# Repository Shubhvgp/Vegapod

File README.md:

Hey Guys, I have created this repository to store what we have accomplished this year and what we did last year as well. 
It is a simple method to keep track of whats going on in Vegapod in each department.
There is a folder named Task Upload, where all recruits from thier respective departments will upload whatever major task they have accomplished.
I want to see this repository being updated everyday.
ALRIGHT, ENOUGH CHATTING, OFF WE GO!!! (to work ofc :] )

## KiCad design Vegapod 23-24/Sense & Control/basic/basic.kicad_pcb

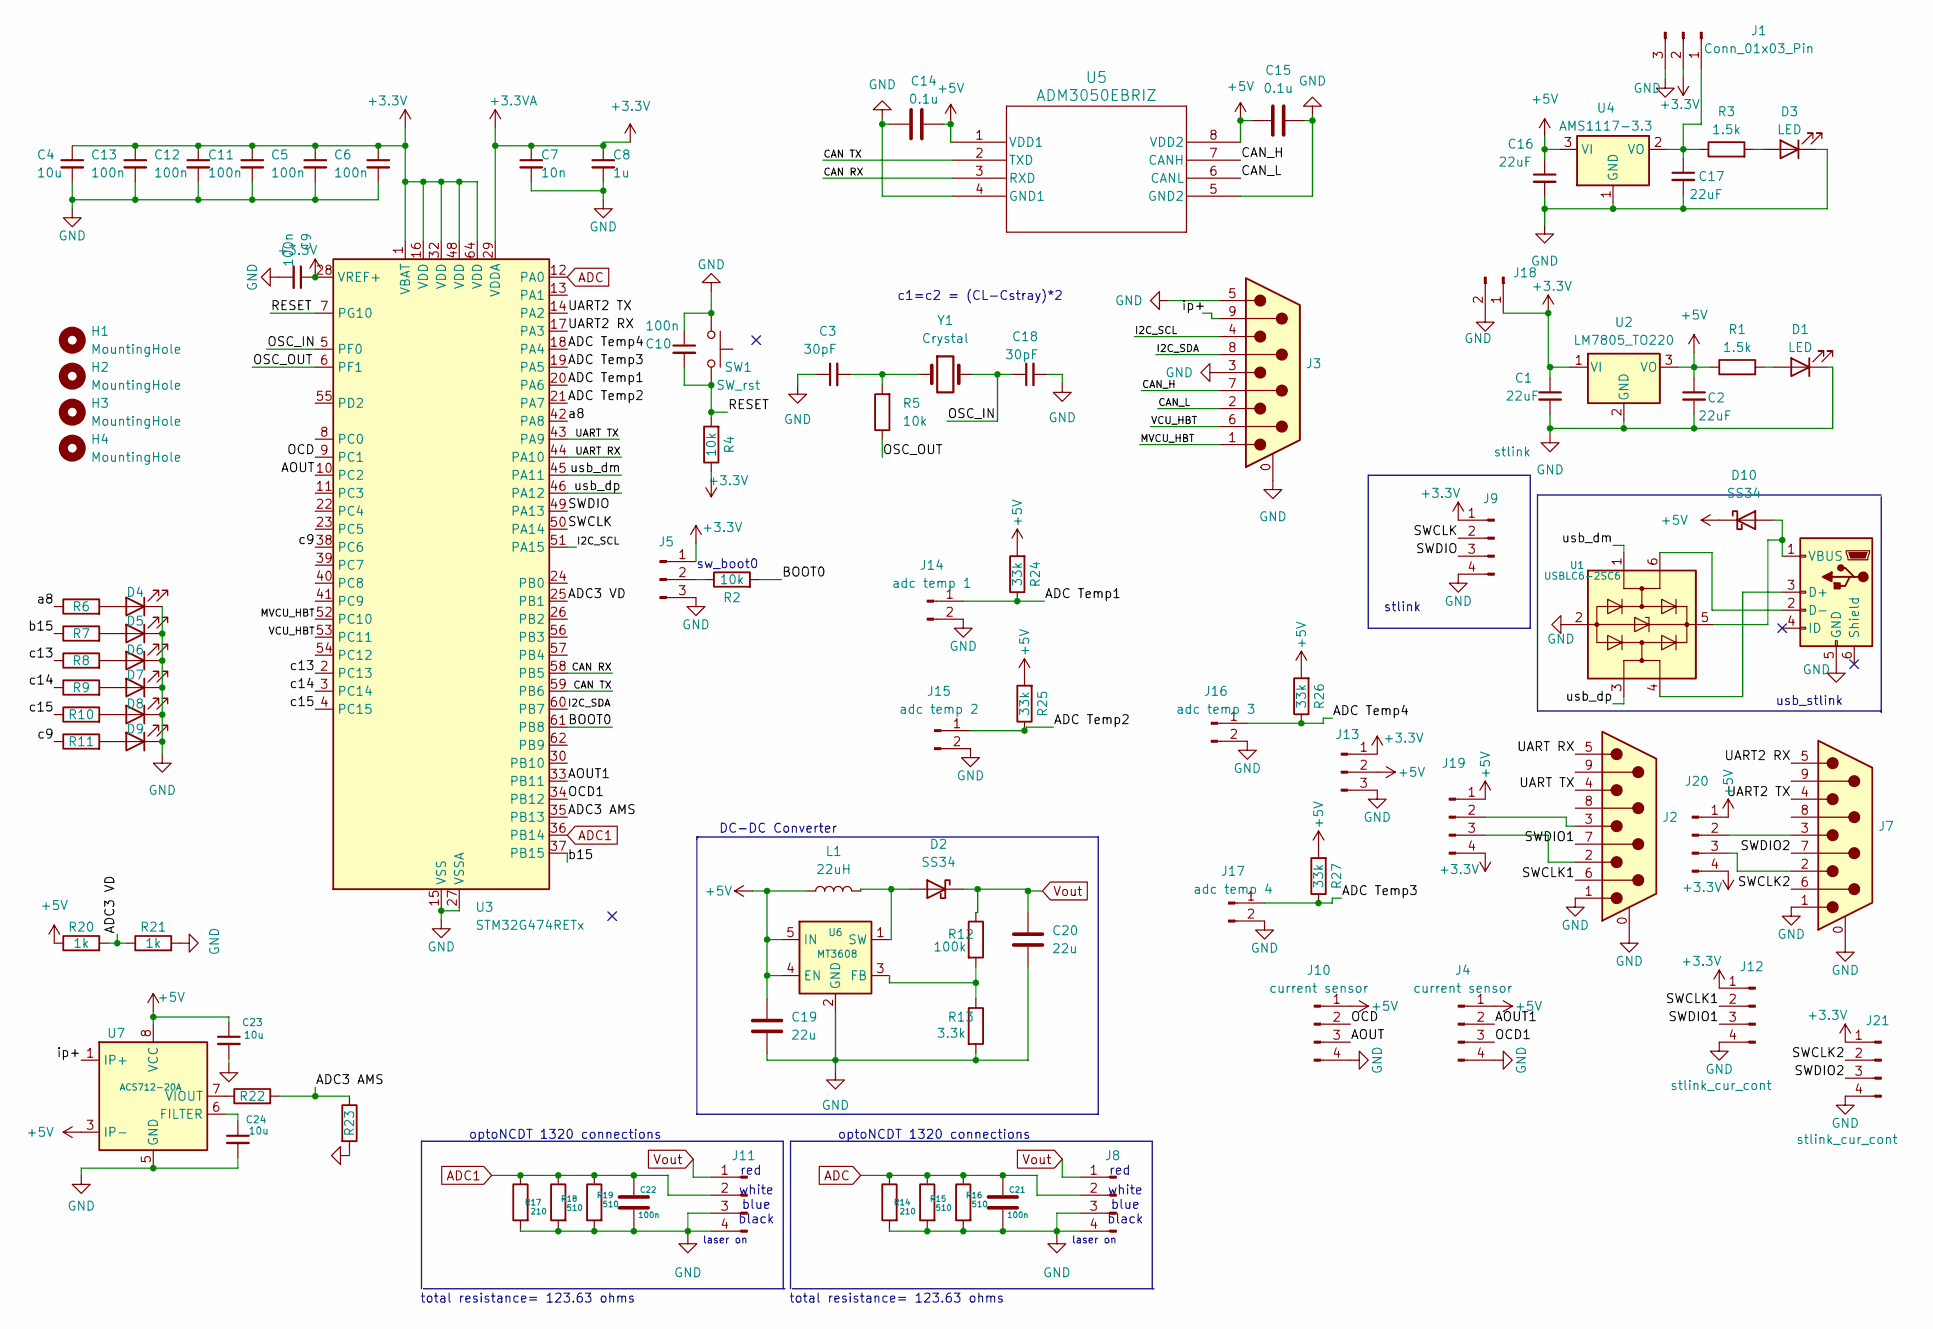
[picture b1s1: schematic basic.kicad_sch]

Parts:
C1, C2, C16, C17: 22uF; C_0805_2012Metric_Pad1.18x1.45mm_HandSolder
C3, C18: 30pF; C_0805_2012Metric_Pad1.18x1.45mm_HandSolder
C4, C23, C24: 10u; C_0805_2012Metric_Pad1.18x1.45mm_HandSolder
C5, C6, C9, C10, C11, C12, C13, C21, C22: 100n; C_0805_2012Metric_Pad1.18x1.45mm_HandSolder
C7: 10n; C_0805_2012Metric_Pad1.18x1.45mm_HandSolder
C8: 1u; C_0805_2012Metric_Pad1.18x1.45mm_HandSolder
C14, C15: 0.1u; C_0805_2012Metric_Pad1.18x1.45mm_HandSolder
C19, C20: 22u; C_1206_3216Metric_Pad1.33x1.80mm_HandSolder
D1, D3, D4, D5, D6, D7, D8, D9: LED; LED_0805_2012Metric_Pad1.15x1.40mm_HandSolder
D2: SS34; D_SMA_Handsoldering
D10: SS34; D_SMA-SMB_Universal_Handsoldering
H1, H2, H3, H4: MountingHole; MountingHole_3.2mm_M3
J1, J5, J13: Conn_01x03_Pin; PinHeader_1x03_P2.54mm_Vertical
J2, J3, J7: DE9_Plug_MountingHoles; DSUB-9_Male_Horizontal_P2.77x2.84mm_EdgePinOffset4.94mm_Hou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
J4, J10: current sensor; TerminalBlock_Phoenix_MKDS-1,5-4_1x04_P5.00mm_Horizontal
J6: USB_B_Micro; USB_Micro-B_Amphenol_10118193-0002LF_Horizontal
J8, J11: conn to air gap sensor; TerminalBlock_Phoenix_MKDS-1,5-4_1x04_P5.00mm_Horizontal
J9: stlink; PinHeader_1x04_P2.54mm_Horizontal
J12, J21: stlink_cur_cont; PinHeader_1x04_P2.54mm_Vertical
J14: adc temp 1; PinHeader_1x02_P2.54mm_Vertical
J15: adc temp 2; PinHeader_1x02_P2.54mm_Vertical
J16: adc temp 3; PinHeader_1x02_P2.54mm_Vertical
J17: adc temp 4; PinHeader_1x02_P2.54mm_Vertical
J18: Conn_01x02_Pin; TerminalBlock_Phoenix_MKDS-1,5-2-5.08_1x02_P5.08mm_Horizont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
J19, J20: current sensor; PinHeader_1x04_P2.54mm_Vertical
L1: 22uH; L_10.4x10.4_H4.8
R1, R3: 1.5k; R_0805_2012Metric_Pad1.20x1.40mm_HandSolder
R2, R4, R5: 10k; R_0805_2012Metric_Pad1.20x1.40mm_HandSolder
R6, R7, R8, R9, R10, R11, R20, R21, R22, R23: 1k; R_0805_2012Metric_Pad1.20x1.40mm_HandSolder
R12: 100k; R_0805_2012Metric_Pad1.20x1.40mm_HandSolder
R13: 3.3k; R_0805_2012Metric_Pad1.20x1.40mm_HandSolder
R14, R17: 210; R_0805_2012Metric_Pad1.20x1.40mm_HandSolder
R15, R16, R18, R19: 510; R_0805_2012Metric_Pad1.20x1.40mm_HandSolder
R24, R25, R26, R27: 33k; R_0805_2012Metric_Pad1.20x1.40mm_HandSolder
SW1: SW_rst; SW_PUSH_6mm_H5mm
U1: USBLC6-2SC6; SOT-23-6
U2: LM7805_TO220; TO-220-3_Vertical
U3: STM32G474RETx; LQFP-64_10x10mm_P0.5mm
U4: AMS1117-3.3; SOT-223-3_TabPin2
U5: ADM3050EBRIZ; RI-8-1_ADI-L
U6: MT3608; SOT-23-6
U7: ACS712-20A; SOIC-8_3.9x4.9mm_P1.27mm
Y1: Crystal; Crystal_HC49-U_Vertical

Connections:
+3.3V: C1.1, C4.1, C5.1, C6.1, C7.1, C8.1, C9.1, C11.1, C12.1, C13.1, J1.2, J5.1, J9.1, J12.1, J13.1, J18.1, J19.4, J20.4, J21.1, R4.1, U2.1 (VI), U3.1 (VBAT), U3.16 (VDD), U3.28 (VREF+), U3.29 (VDDA), U3.32 (VDD), U3.48 (VDD), U3.64 (VDD)
+5V: C2.1, C14.2, C15.2, C16.1, C19.1, C23.1, D10.1 (K), J4.1, J10.1, J13.2, J19.1, J20.1, L1.1, R1.1, R20.1, R24.2, R25.2, R26.2, R27.2, U2.3 (VO), U4.3 (VI), U5.1 (VDD1), U5.8 (VDD2), U6.4 (EN), U6.5 (IN), U7.3 (IP-), U7.4 (IP-), U7.8 (VCC)
/ADC3 AMS: R22.2, R23.1, U3.35 (PB13)
/ADC3 VD: R20.2, R21.1, U3.25 (PB1)
/ADC Temp1: J14.1, R24.1, U3.20 (PA6)
/ADC Temp2: J15.1, R25.1, U3.21 (PA7)
/ADC Temp3: J17.1, R27.1, U3.19 (PA5)
/ADC Temp4: J16.1, R26.1, U3.18 (PA4)
/AOUT: J10.3, U3.10 (PC2)
/AOUT1: J4.2, U3.33 (PB11)
/BOOT0: R2.2, U3.61 (PB8)
/CAN RX: U3.58 (PB5), U5.3 (RXD)
/CAN TX: U3.59 (PB6), U5.2 (TXD)
/CAN_H: J3.7, U5.7 (CANH)
/CAN_L: J3.2, U5.6 (CANL)
/I2C_SCL: J3.4, U3.51 (PA15)
/I2C_SDA: J3.8, U3.60 (PB7)
/MVCU_HBT: J3.1, U3.52 (PC10)
/OCD: J10.2, U3.9 (PC1)
/OCD1: J4.3, U3.34 (PB12)
/OSC_IN: C18.1, U3.5 (PF0), Y1.2
/OSC_OUT: R5.1, U3.6 (PF1)
/RESET: C10.2, R4.2, SW1.2, U3.7 (PG10)
/SWCLK: J9.2, U3.50 (PA14)
/SWCLK1: J2.6, J12.2
/SWCLK2: J7.6, J21.2
/SWDIO: J9.3, U3.49 (PA13)
/SWDIO1: J2.7, J12.3
/SWDIO2: J7.7, J21.3
/UART2 RX: J7.5, U3.17 (PA3)
/UART2 TX: J7.4, U3.14 (PA2)
/UART RX: J2.5, U3.44 (PA10)
/UART TX: J2.4, U3.43 (PA9)
/VCU_HBT: J3.6, U3.53 (PC11)
/a8: R6.1, U3.42 (PA8)
/b15: R7.1, U3.37 (PB15)
/c9: R11.1, U3.38 (PC6)
/c13: R8.1, U3.2 (PC13)
/c14: R9.1, U3.3 (PC14)
/c15: R10.1, U3.4 (PC15)
/ip+: J3.9, U7.1 (IP+), U7.2 (IP+)
/usb_dm: U1.1 (I/O1), U3.45 (PA11)
/usb_dp: U1.3 (I/O2), U3.46 (PA12)
ADC: C21.1, J8.2, R14.1, R15.1, R16.1, U3.12 (PA0)
ADC1: C22.1, J11.2, R17.1, R18.1, R19.1, U3.36 (PB14)
GND: C1.2, C2.2, C3.1, C4.2, C5.2, C6.2, C7.2, C8.2, C9.2, C10.1, C11.2, C12.2, C13.2, C14.1, C15.1, C16.2, C17.2, C18.2, C19.2, C20.2, C21.2, C22.2, C23.2, C24.2, D1.1 (K), D3.1 (K), D4.1 (K), D5.1 (K), D6.1 (K), D7.1 (K), D8.1 (K), D9.1 (K), J1.3, J2.0 (PAD), J2.1, J3.0 (PAD), J3.3, J3.5, J4.4, J5.3, J6.5 (GND), J7.0 (PAD), J7.1, J8.3, J8.4, J9.4, J10.4, J11.3, J11.4, J12.4, J13.3, J14.2, J15.2, J16.2, J17.2, J18.2, J21.4, R13.2, R14.2, R15.2, R16.2, R17.2, R18.2, R19.2, R21.2, R23.2, SW1.1, U1.2 (GND), U2.2 (GND), U3.15 (VSS), U3.27 (VSSA), U3.31 (VSS), U3.47 (VSS), U3.63 (VSS), U4.1 (GND), U5.4 (GND1), U5.5 (GND2), U6.2 (GND), U7.5 (GND)
unnamed: C3.2, R5.2, Y1.1
unnamed: D1.2 (A), R1.2
unnamed: D2.2 (A), L1.2, U6.1 (SW)
unnamed: D3.2 (A), R3.2
unnamed: D4.2 (A), R6.2
unnamed: D5.2 (A), R7.2
unnamed: D6.2 (A), R8.2
unnamed: D7.2 (A), R9.2
unnamed: D8.2 (A), R10.2
unnamed: D9.2 (A), R11.2
unnamed: D10.2 (A), J6.1 (VBUS), U1.5 (VBUS)
unnamed: C17.1, J1.1, R3.1, U4.2 (VO)
unnamed: J5.2, R2.1
unnamed: J6.3 (D+), U1.4 (I/O2)
unnamed: J6.2 (D-), U1.6 (I/O1)
unnamed: J2.3, J19.2
unnamed: J2.2, J19.3
unnamed: J7.3, J20.2
unnamed: J7.2, J20.3
unnamed: R12.2, R13.1, U6.3 (FB)
unnamed: C24.1, U7.6 (FILTER)
unnamed: R22.1, U7.7 (VIOUT)
Vout: C20.1, D2.1 (K), J8.1, J11.1, R12.1

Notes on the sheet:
optoNCDT 1320 connections
DC-DC Converter
laser on
white blue black
red
sw_boot0
total resistance= 123.63 ohms
usb_stlink
stlink
c1=c2 = (CL-Cstray)*2

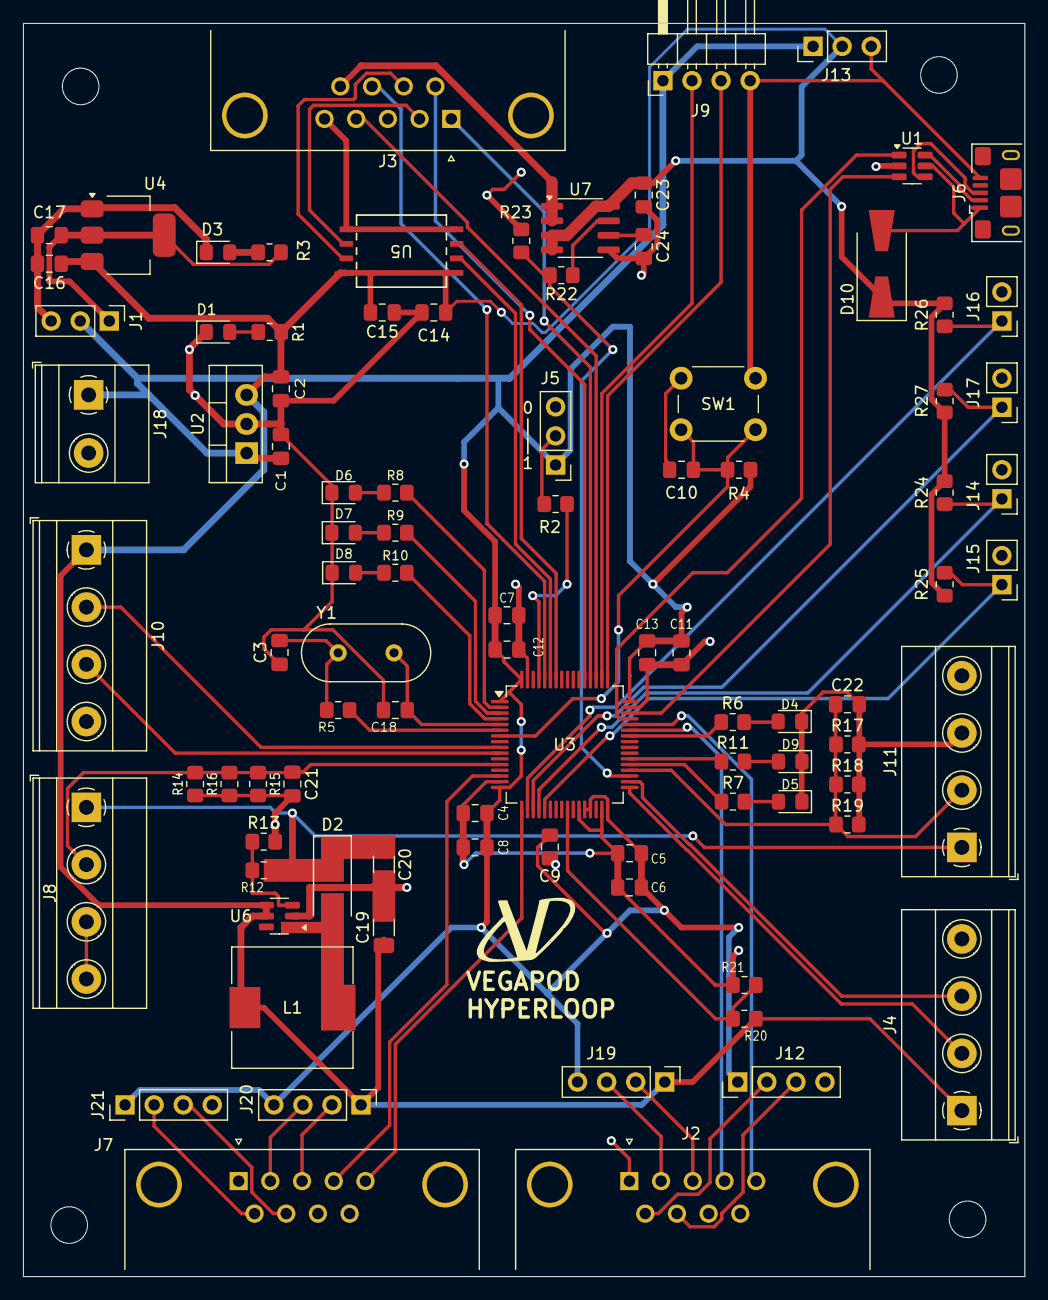
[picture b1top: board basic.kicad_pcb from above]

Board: 2 copper layers, 87.5 x 109.5 mm, 96 parts (0 on the bottom side), 69 nets.

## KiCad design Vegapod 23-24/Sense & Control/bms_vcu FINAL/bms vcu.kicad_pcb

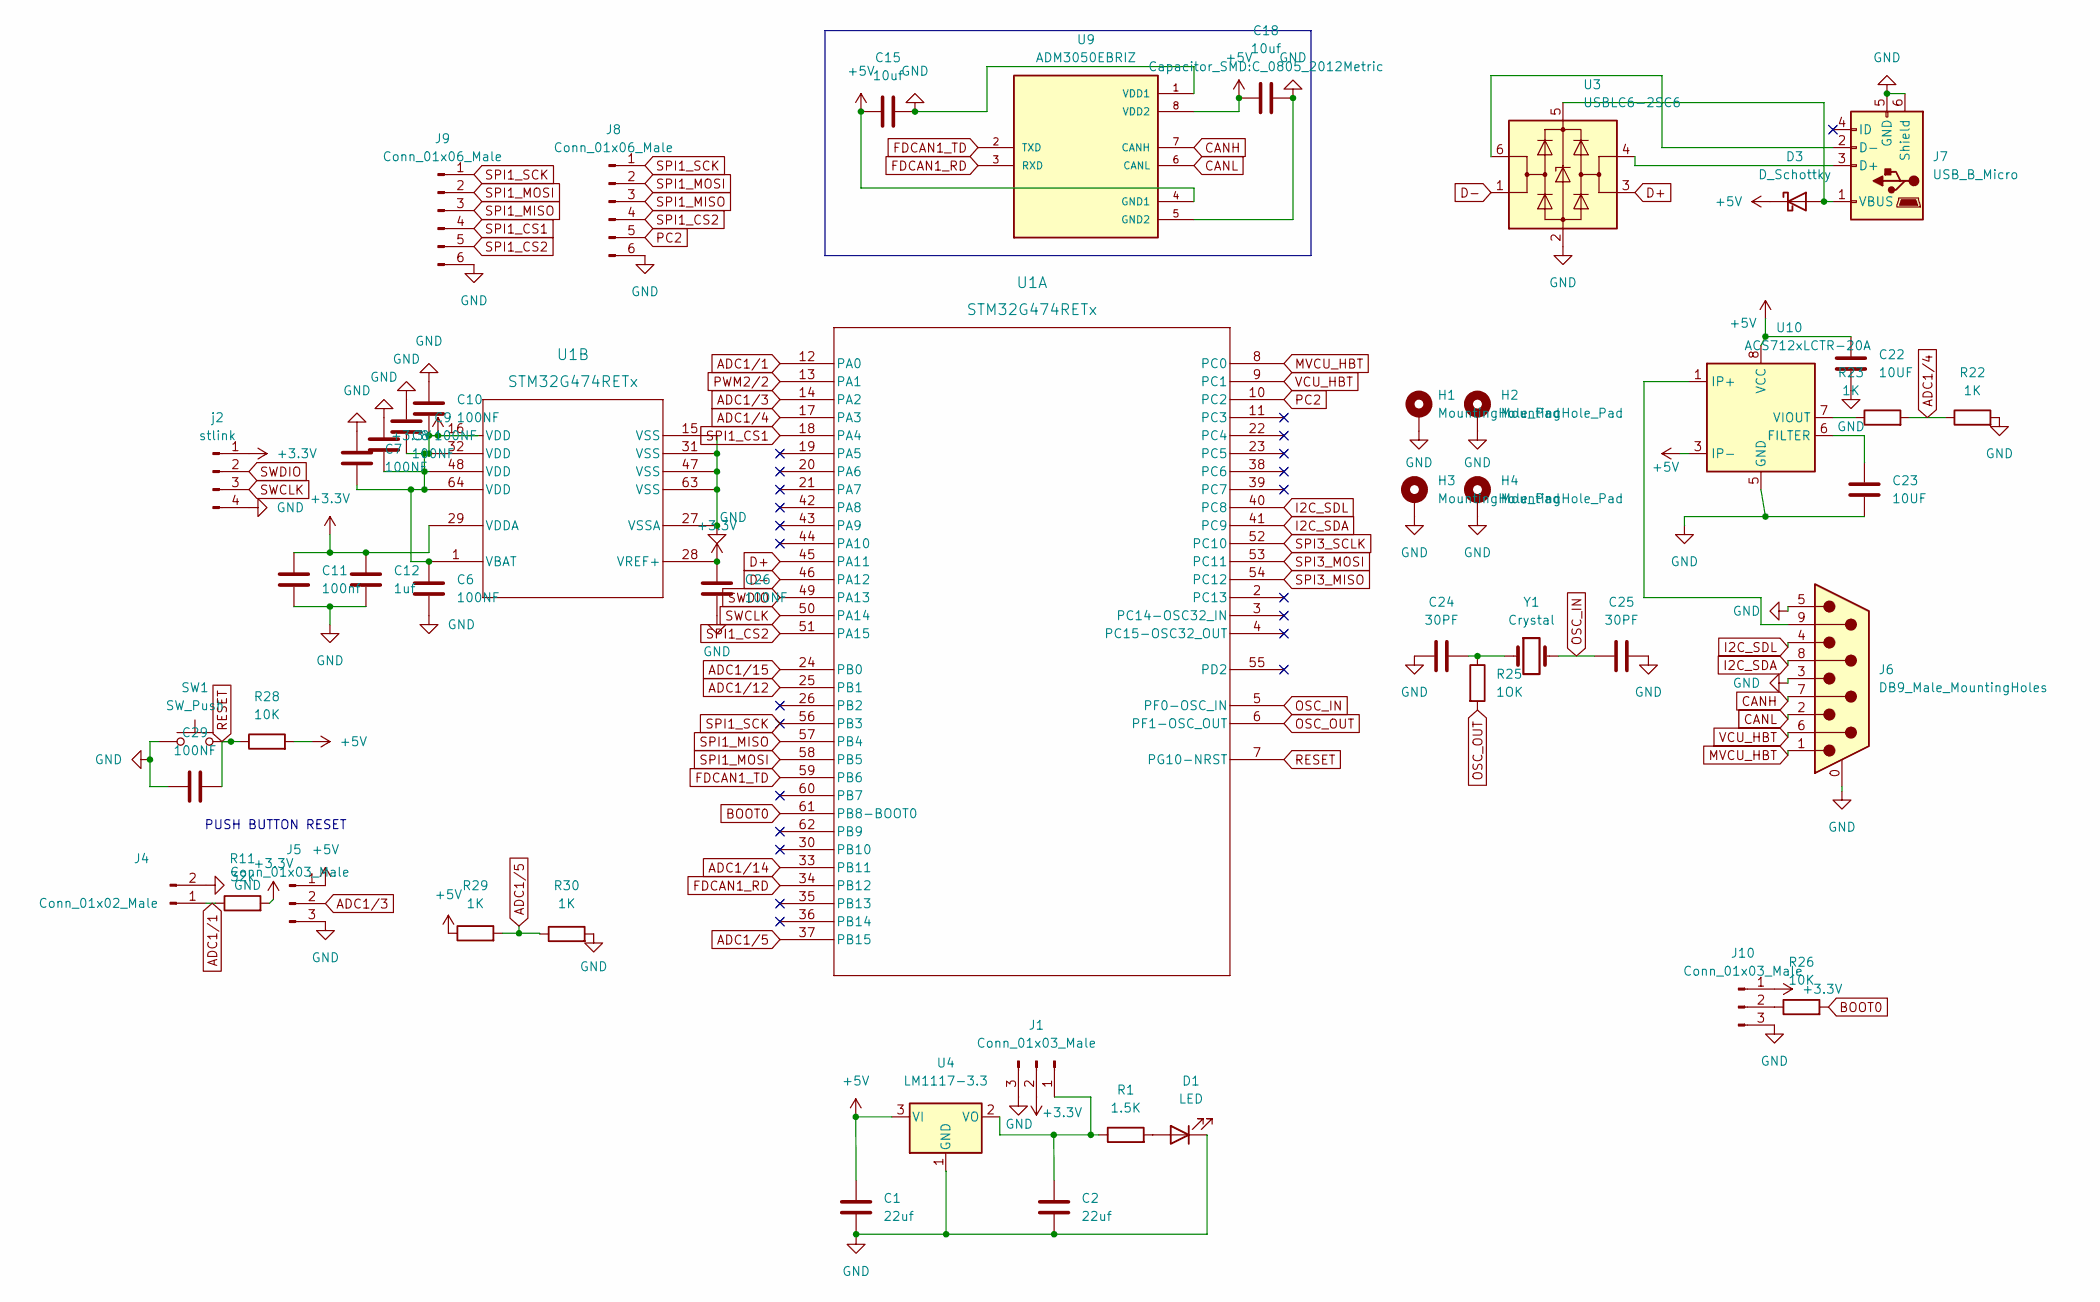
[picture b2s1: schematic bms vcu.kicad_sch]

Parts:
C1, C2: 22uf; C_0805_2012Metric
C6, C7, C8, C9, C10, C26: 100NF; C_0805_2012Metric
C11: 100nf; C_0805_2012Metric
C12: 1uf; C_0805_2012Metric
C15, C18: 10uf; C_0805_2012Metric
C22, C23: 10UF; C_1206_3216Metric
C24, C25: 30PF; C_1206_3216Metric
C29: 100NF; C_1206_3216Metric
D1: LED; LED_0603_1608Metric
D3: D_Schottky; D_2010_5025Metric
H1, H2, H3, H4: MountingHole_Pad; MountingHole_3.2mm_M3
J1, J5: Conn_01x03_Male; PinHeader_1x03_P2.54mm_Vertical
J4: Conn_01x02_Male; PinHeader_1x02_P2.54mm_Vertical
J6: DB9_Male_MountingHoles; DSUB-9_Male_Horizontal_P2.77x2.84mm_EdgePinOffset4.94mm_Hou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
J7: USB_B_Micro; USB_Micro-B_Wuerth_629105150521_CircularHoles
J8, J9: Conn_01x06_Male; JST_EH_B6B-EH-A_1x06_P2.50mm_Vertical
J10: Conn_01x03_Male; PinSocket_1x03_P2.54mm_Vertical
R1: 1.5K; R_0805_2012Metric
R11: 32k; R_0805_2012Metric
R22, R23: 1K; R_0805_2012Metric
R25: 1OK; R_1206_3216Metric
R26: 10K; R_0805_2012Metric
R28: 10K; R_1206_3216Metric
R29, R30: 1K; R_1206_3216Metric
SW1: SW_Push; SW_PUSH_6mm
U1: STM32G474RETx; LQFP64-10x10mm
U3: USBLC6-2SC6; SOT-23-6
U4: LM1117-3.3; SOT-223-3_TabPin2
U9: ADM3050EBRIZ; SOIC127P1031X265-8N; PARTREV B
U10: ACS712xLCTR-20A; SOIC-8_3.9x4.9mm_P1.27mm
Y1: Crystal; Crystal_HC18-U_Vertical
j2: stlink; PinHeader_1x04_P2.54mm_Vertical

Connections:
+3.3V: C6.1, C7.2, C8.2, C9.2, C10.2, C11.1, C12.1, C26.1, J1.2, J10.1, R11.2, U1.1 (VBAT), U1.16 (VDD), U1.28 (VREF+), U1.29 (VDDA), U1.32 (VDD), U1.48 (VDD), U1.64 (VDD), j2.1
+5V: C1.1, C15.1, C18.1, C22.1, D3.1 (K), J5.1, R28.2, R29.1, U4.3 (VI), U9.4 (GND1), U9.8 (VDD2), U10.3 (IP-), U10.4 (IP-), U10.8 (VCC)
ADC1/1: J4.1, R11.1, U1.12 (PA0)
ADC1/3: J5.2, U1.14 (PA2)
ADC1/4: R22.1, R23.2, U1.17 (PA3)
ADC1/5: R29.2, R30.1, U1.37 (PB15)
ADC1/12: U1.25 (PB1)
ADC1/14: U1.33 (PB11)
ADC1/15: U1.24 (PB0)
BOOT0: R26.2, U1.61 (PB8-BOOT0)
CANH: J6.7, U9.7 (CANH)
CANL: J6.2, U9.6 (CANL)
D+: U1.45 (PA11), U3.3 (I/O2)
D-: U1.46 (PA12), U3.1 (I/O1)
FDCAN1_RD: U1.34 (PB12), U9.3 (RXD)
FDCAN1_TD: U1.59 (PB6), U9.2 (TXD)
GND: C1.2, C2.2, C6.2, C7.1, C8.1, C9.1, C10.1, C11.2, C12.2, C15.2, C18.2, C22.2, C23.2, C24.1, C25.2, C26.2, C29.1, D1.1 (K), H1.1, H2.1, H3.1, H4.1, J1.3, J4.2, J5.3, J6.0 (PAD), J6.3, J6.5, J7.5 (GND), J7.6 (Shield), J8.6, J9.6, J10.3, R22.2, R30.2, SW1.1, U1.15 (VSS), U1.27 (VSSA), U1.31 (VSS), U1.47 (VSS), U1.63 (VSS), U3.2 (GND), U4.1 (GND), U9.1 (VDD1), U9.5 (GND2), U10.5 (GND), j2.4
I2C_SDA: J6.8, U1.41 (PC9)
I2C_SDL: J6.4, U1.40 (PC8)
MVCU_HBT: J6.1, U1.8 (PC0)
unnamed: C2.1, J1.1, R1.1, U4.2 (VO)
unnamed: C23.1, U10.6 (FILTER)
unnamed: C24.2, R25.1, Y1.1
unnamed: D1.2 (A), R1.2
unnamed: D3.2 (A), J7.1 (VBUS), U3.5 (VBUS)
unnamed: J6.9, U10.1 (IP+), U10.2 (IP+)
unnamed: J7.2 (D-), U3.6 (I/O1)
unnamed: J7.3 (D+), U3.4 (I/O2)
unnamed: J10.2, R26.1
unnamed: R23.1, U10.7 (VIOUT)
OSC_IN: C25.1, U1.5 (PF0-OSC_IN), Y1.2
OSC_OUT: R25.2, U1.6 (PF1-OSC_OUT)
PC2: J8.5, U1.10 (PC2)
PWM2/2: U1.13 (PA1)
RESET: C29.2, R28.1, SW1.2, U1.7 (PG10-NRST)
SPI1_CS1: J9.4, U1.18 (PA4)
SPI1_CS2: J8.4, J9.5, U1.51 (PA15)
SPI1_MISO: J8.3, J9.3, U1.57 (PB4)
SPI1_MOSI: J8.2, J9.2, U1.58 (PB5)
SPI1_SCK: J8.1, J9.1, U1.56 (PB3)
SPI3_MISO: U1.54 (PC12)
SPI3_MOSI: U1.53 (PC11)
SPI3_SCLK: U1.52 (PC10)
SWCLK: U1.50 (PA14), j2.3
SWDIO: U1.49 (PA13), j2.2
VCU_HBT: J6.6, U1.9 (PC1)

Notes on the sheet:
PUSH BUTTON RESET

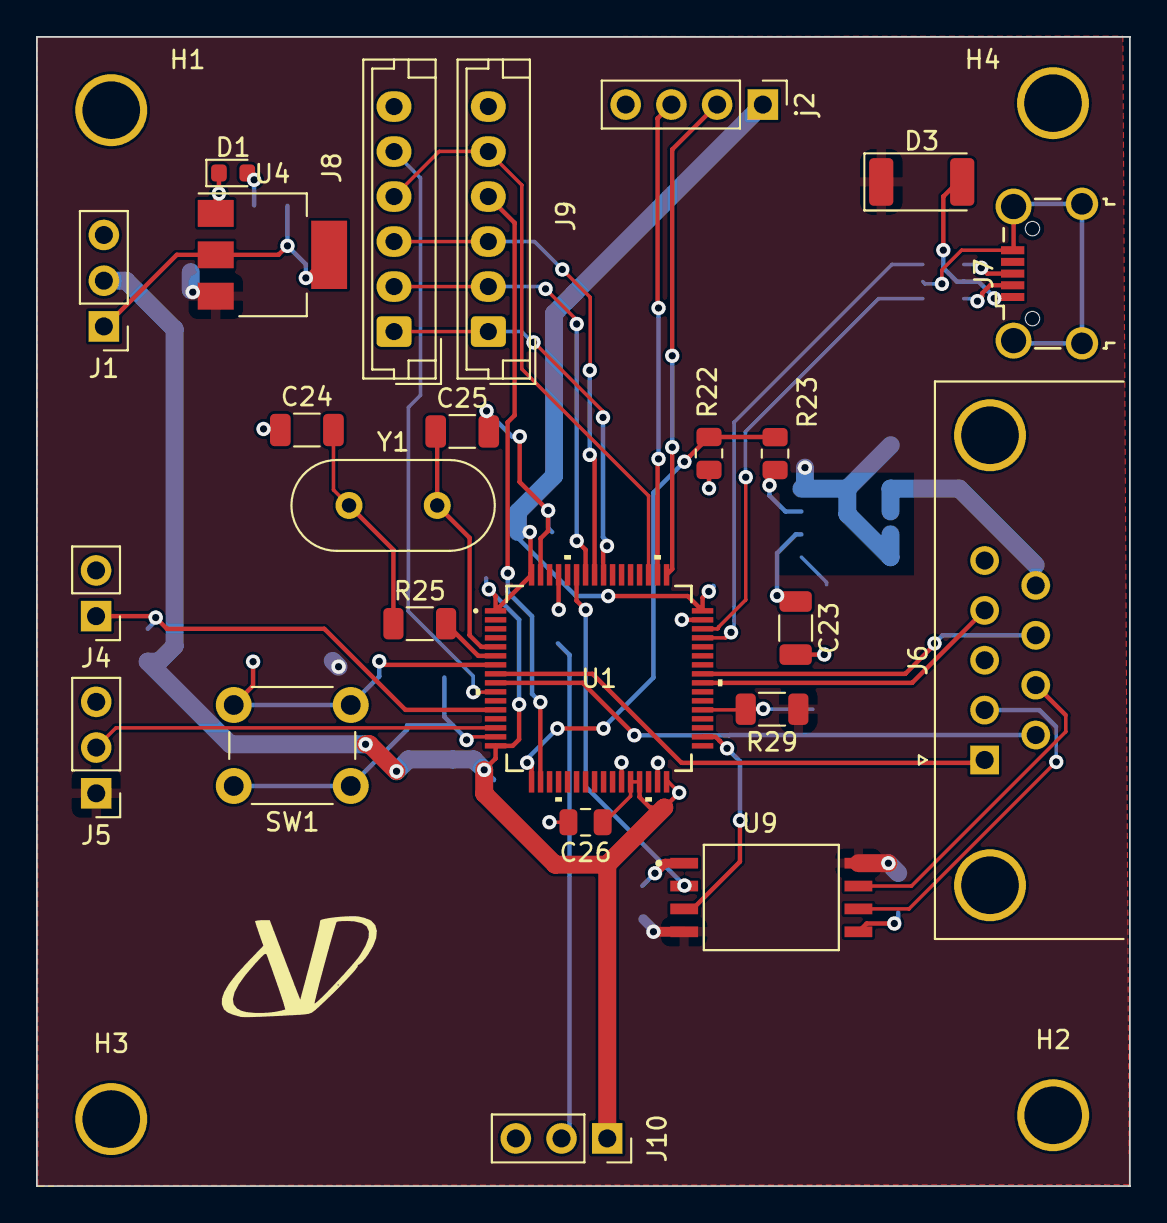
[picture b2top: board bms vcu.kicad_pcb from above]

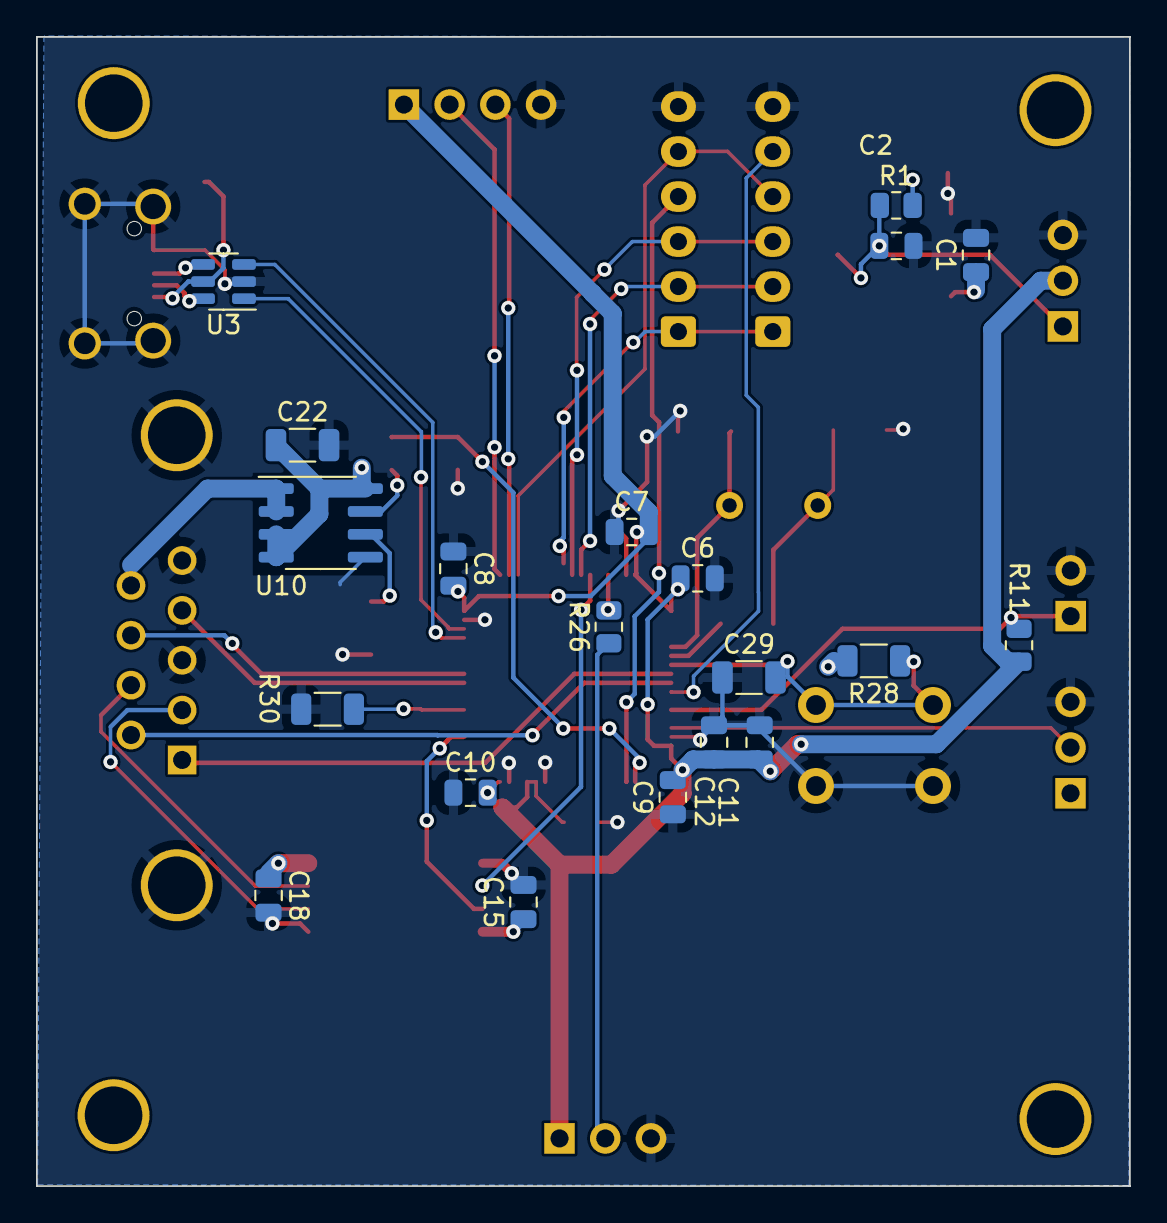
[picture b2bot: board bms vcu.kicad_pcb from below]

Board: 2 copper layers, 60.7 x 63.8 mm, 48 parts (20 on the bottom side), 39 nets.

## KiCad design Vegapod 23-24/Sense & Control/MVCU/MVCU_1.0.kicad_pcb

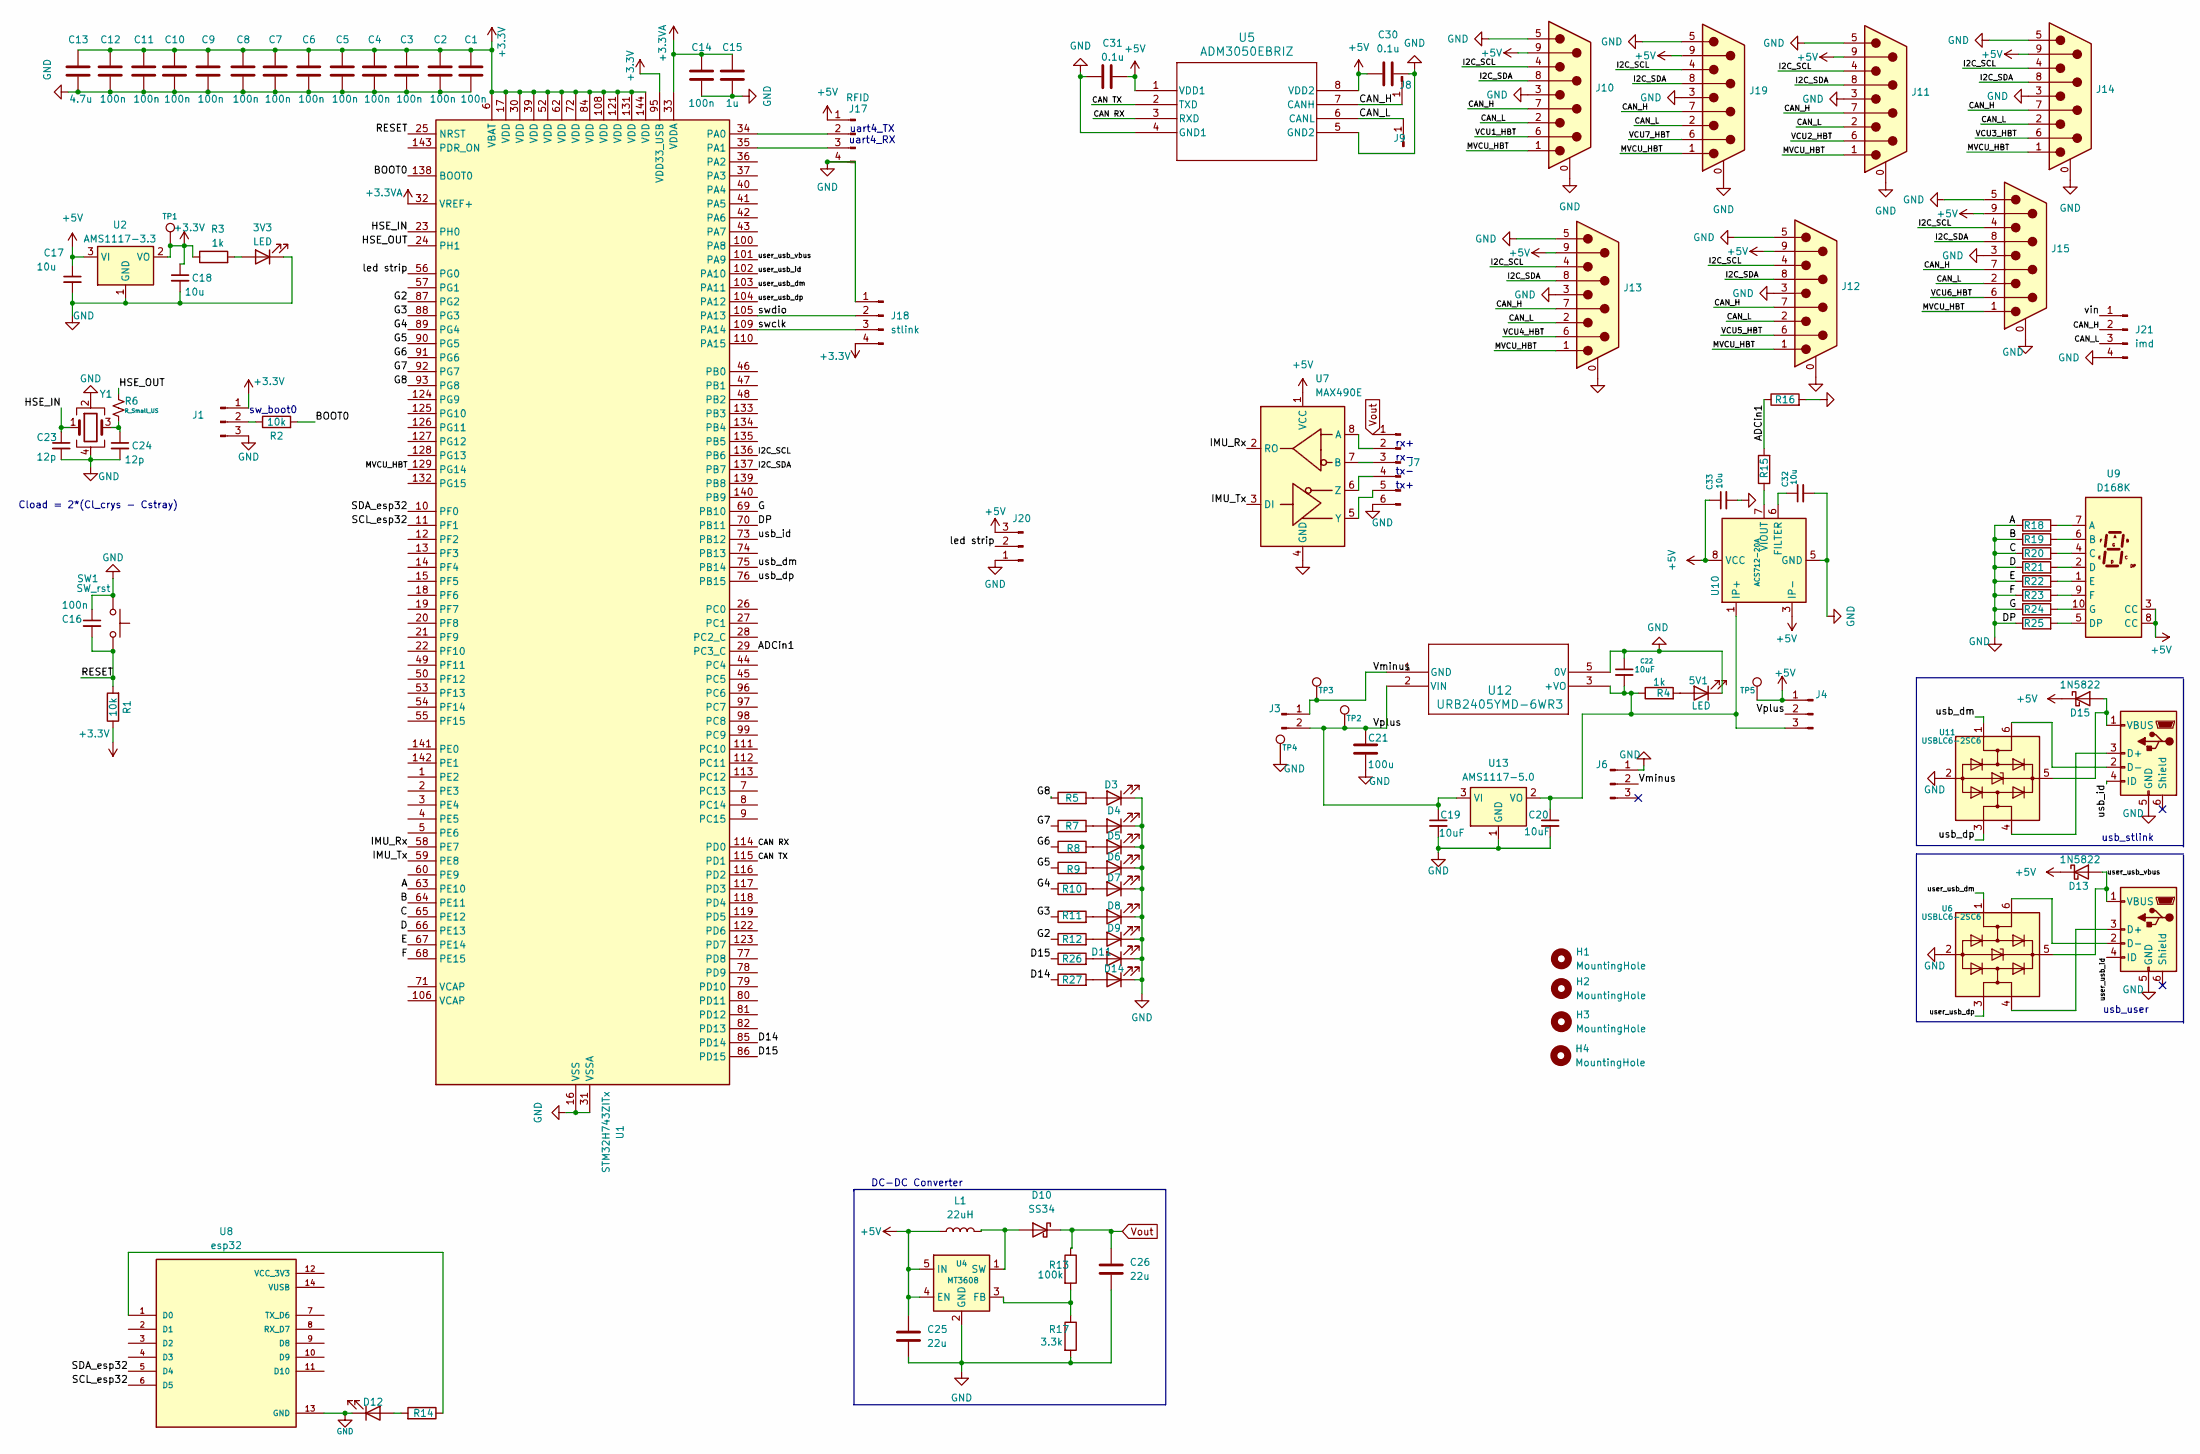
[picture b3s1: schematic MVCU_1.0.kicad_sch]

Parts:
3V3, 5V1: LED; LED_0805_2012Metric_Pad1.15x1.40mm_HandSolder
C1, C2, C3, C4, C5, C6, C7, C8, C9, C10, C11, C12, C14, C16: 100n; C_0805_2012Metric_Pad1.18x1.45mm_HandSolder
C13: 4.7u; C_0805_2012Metric_Pad1.18x1.45mm_HandSolder
C15: 1u; C_0805_2012Metric_Pad1.18x1.45mm_HandSolder
C17, C18, C32, C33: 10u; C_0805_2012Metric_Pad1.18x1.45mm_HandSolder
C19, C20: 10uF; C_0805_2012Metric_Pad1.18x1.45mm_HandSolder
C21: 100u; CP_Radial_D8.0mm_P2.50mm
C22: 10uF; CP_Radial_D8.0mm_P2.50mm
C23, C24: 12p; C_0805_2012Metric_Pad1.18x1.45mm_HandSolder
C25, C26: 22u; C_1206_3216Metric_Pad1.33x1.80mm_HandSolder
C30, C31: 0.1u; C_0805_2012Metric_Pad1.18x1.45mm_HandSolder
D3, D4, D5, D6, D7, D8, D9, D11, D12, D14: LED; LED_0805_2012Metric_Pad1.15x1.40mm_HandSolder
D10: SS34; D_SMA_Handsoldering
D13, D15: 1N5822; D_DO-201AD_P15.24mm_Horizontal
H1, H2, H3, H4: MountingHole; MountingHole_3.2mm_M3
J1: Conn_01x03_Pin; PinHeader_1x03_P2.54mm_Vertical
J3: Conn_01x02_Pin; TerminalBlock_Phoenix_MKDS-1,5-2-5.08_1x02_P5.08mm_Horizont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
J4, J6: Conn_01x03_Pin; PinSocket_1x03_P2.54mm_Vertical
J7: Conn_01x06_Pin; TerminalBlock_Phoenix_MKDS-1,5-6-5.08_1x06_P5.08mm_Horizont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
J8, J9: Conn_01x01_Pin; PinHeader_1x01_P2.54mm_Vertical
J10, J11, J12, J13, J14, J15, J19: DE9_Plug_MountingHoles; DSUB-9_Male_Horizontal_P2.77x2.84mm_EdgePinOffset4.94mm_Hou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
J16, J22: USB_B_Micro; USB_Micro-B_Amphenol_10103594-0001LF_Horizontal
J17: RFID; PinHeader_1x04_P2.54mm_Vertical
J18: stlink; PinHeader_1x04_P2.54mm_Vertical
J20: Conn_01x03_Pin; TerminalBlock_Phoenix_MKDS-1,5-3-5.08_1x03_P5.08mm_Horizont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
J21: imd; PinHeader_1x04_P2.54mm_Vertical
L1: 22uH; L_10.4x10.4_H4.8
R1, R2: 10k; R_0805_2012Metric_Pad1.20x1.40mm_HandSolder
R3, R4, R5, R7, R8, R9, R10, R11, R12, R14, R15, R16, R26, R27: 1k; R_0805_2012Metric_Pad1.20x1.40mm_HandSolder
R6: R_Small_US; R_0805_2012Metric_Pad1.20x1.40mm_HandSolder
R13: 100k; R_0805_2012Metric_Pad1.20x1.40mm_HandSolder
R17: 3.3k; R_0805_2012Metric_Pad1.20x1.40mm_HandSolder
R18, R19, R20, R21, R22, R23, R24, R25: 220; R_0805_2012Metric_Pad1.20x1.40mm_HandSolder
SW1: SW_rst; SW_PUSH_6mm_H5mm
TP1, TP2, TP3, TP4, TP5: TestPoint; TestPoint_Keystone_5010-5014_Multipurpose
U1: STM32H743ZITx; LQFP-144_20x20mm_P0.5mm
U2: AMS1117-3.3; SOT-223-3_TabPin2
U4: MT3608; SOT-23-6
U5: ADM3050EBRIZ; RI-8-1_ADI-M
U6, U11: USBLC6-2SC6; SOT-23-6
U7: MAX490E; SOIC-8_3.9x4.9mm_P1.27mm
U8: esp32; MODULE_113991054; PARTREV 23/05/2022
U9: D168K; D1X8K
U10: ACS712-20A; SOIC-8_3.9x4.9mm_P1.27mm
U12: URB2405YMD-6WR3; URB_YMD-6WR3_MNS
U13: AMS1117-5.0; SOT-223-3_TabPin2
Y1: Crystal_GND24; Crystal_SMD_3225-4Pin_3.2x2.5mm_HandSoldering

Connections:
+3.3V: C1.1, C2.1, C3.1, C4.1, C5.1, C6.1, C7.1, C8.1, C9.1, C10.1, C11.1, C12.1, C13.1, C18.1, J1.1, J18.4, R1.1, R3.1, TP1.1, U1.6 (VBAT), U1.17 (VDD), U1.30 (VDD), U1.39 (VDD), U1.52 (VDD), U1.62 (VDD), U1.72 (VDD), U1.84 (VDD), U1.95 (VDD33_USB), U1.108 (VDD), U1.121 (VDD), U1.131 (VDD), U1.144 (VDD), U2.2 (VO)
+3.3VA: C14.1, C15.1, U1.32 (VREF+), U1.33 (VDDA)
+5V: C17.1, C25.1, C30.2, C31.2, C33.1, D13.1 (K), D15.1 (K), J4.1, J10.9, J11.9, J12.9, J13.9, J14.9, J15.9, J17.1, J19.9, J20.3, L1.1, TP5.1, U2.3 (VI), U4.4 (EN), U4.5 (IN), U5.1 (VDD1), U5.8 (VDD2), U7.1 (VCC), U9.3 (CC), U9.8 (CC), U10.3 (IP-), U10.4 (IP-), U10.8 (VCC)
/ADCin1: R15.2, R16.1, U1.29 (PC3_C)
/BOOT0: R2.2, U1.138 (BOOT0)
/CAN RX: U1.114 (PD0), U5.3 (RXD)
/CAN TX: U1.115 (PD1), U5.2 (TXD)
/CAN_H: J8.1, J10.7, J11.7, J12.7, J13.7, J14.7, J15.7, J19.7, J21.2, U5.7 (CANH)
/CAN_L: J9.1, J10.2, J11.2, J12.2, J13.2, J14.2, J15.2, J19.2, J21.3, U5.6 (CANL)
/D14: R27.1, U1.85 (PD14)
/D15: R26.1, U1.86 (PD15)
/G2: R12.1, U1.87 (PG2)
/G3: R11.1, U1.88 (PG3)
/G4: R10.1, U1.89 (PG4)
/G5: R9.1, U1.90 (PG5)
/G6: R8.1, U1.91 (PG6)
/G7: R7.1, U1.92 (PG7)
/G8: R5.1, U1.93 (PG8)
/HSE_IN: C23.1, U1.23 (PH0), Y1.1
/HSE_OUT: R6.1, U1.24 (PH1)
/I2C_SCL: J10.4, J11.4, J12.4, J13.4, J14.4, J15.4, J19.4, U1.136 (PB6)
/I2C_SDA: J10.8, J11.8, J12.8, J13.8, J14.8, J15.8, J19.8, U1.137 (PB7)
/IMU_Rx: U1.58 (PE7), U7.2 (RO)
/IMU_Tx: U1.59 (PE8), U7.3 (DI)
/MVCU_HBT: J10.1, J11.1, J12.1, J13.1, J14.1, J15.1, J19.1, U1.129 (PG14)
/RESET: C16.2, R1.2, SW1.2, U1.25 (NRST)
/SCL_esp32: U1.11 (PF1), U8.6 (D5)
/SDA_esp32: U1.10 (PF0), U8.5 (D4)
/VCU1_HBT: J10.6
/VCU2_HBT: J11.6
/VCU3_HBT: J14.6
/VCU4_HBT: J13.6
/VCU5_HBT: J12.6
/VCU6_HBT: J15.6
/VCU7_HBT: J19.6
/Vminus: J3.1, J6.2, TP3.1, U12.1 (GND)
/Vplus: C19.1, C21.1, J3.2, J4.2, TP2.1, U12.2 (VIN), U13.3 (VI)
/led strip: J20.2, U1.56 (PG0)
/swclk: J18.3, U1.109 (PA14)
/swdio: J18.2, U1.105 (PA13)
/usb_dm: U1.75 (PB14), U11.1 (I/O1)
/usb_dp: U1.76 (PB15), U11.3 (I/O2)
/usb_id: J22.4 (ID), U1.73 (PB12)
/user_usb_dm: U1.103 (PA11), U6.1 (I/O1)
/user_usb_dp: U1.104 (PA12), U6.3 (I/O2)
/user_usb_id: J16.4 (ID), U1.102 (PA10)
/user_usb_vbus: D13.2 (A), J16.1 (VBUS), U1.101 (PA9), U6.5 (VBUS)
/vin: J21.1
GND: 3V3.1 (K), 5V1.1 (K), C1.2, C2.2, C3.2, C4.2, C5.2, C6.2, C7.2, C8.2, C9.2, C10.2, C11.2, C12.2, C13.2, C14.2, C15.2, C16.1, C17.2, C18.2, C19.2, C20.2, C21.2, C22.1, C23.2, C24.2, C25.2, C26.2, C30.1, C31.1, C32.2, C33.2, D3.1 (K), D4.1 (K), D5.1 (K), D6.1 (K), D7.1 (K), D8.1 (K), D9.1 (K), D11.1 (K), D12.1 (K), D14.1 (K), J1.3, J6.1, J7.6, J10.0 (PAD), J10.3, J10.5, J11.0 (PAD), J11.3, J11.5, J12.0 (PAD), J12.3, J12.5, J13.0 (PAD), J13.3, J13.5, J14.0 (PAD), J14.3, J14.5, J15.0 (PAD), J15.3, J15.5, J16.5 (GND), J17.4, J18.1, J19.0 (PAD), J19.3, J19.5, J20.1, J21.4, J22.5 (GND), R16.2, R17.2, R18.1, R19.1, R20.1, R21.1, R22.1, R23.1, R24.1, R25.1, SW1.1, TP4.1, U1.16 (VSS), U1.31 (VSSA), U1.38 (VSS), U1.51 (VSS), U1.61 (VSS), U1.63 (PE10), U1.64 (PE11), U1.65 (PE12), U1.66 (PE13), U1.67 (PE14), U1.68 (PE15), U1.69 (PB10), U1.70 (PB11), U1.83 (VSS), U1.94 (VSS), U1.107 (VSS), U1.120 (VSS), U1.130 (VSS), U2.1 (GND), U4.2 (GND), U5.4 (GND1), U5.5 (GND2), U6.2 (GND), U7.4 (GND), U8.13 (GND), U10.5 (GND), U11.2 (GND), U12.5 (0V), U13.1 (GND), Y1.2, Y1.4
unnamed: 3V3.2 (A), R3.2
unnamed: 5V1.2 (A), R4.2
unnamed: C24.1, R6.2, Y1.3
unnamed: D3.2 (A), R5.2
unnamed: D4.2 (A), R7.2
unnamed: D5.2 (A), R8.2
unnamed: D6.2 (A), R9.2
unnamed: D7.2 (A), R10.2
unnamed: D8.2 (A), R11.2
unnamed: D9.2 (A), R12.2
unnamed: D10.2 (A), L1.2, U4.1 (SW)
unnamed: D11.2 (A), R26.2
unnamed: D12.2 (A), R14.2
unnamed: D14.2 (A), R27.2
unnamed: D15.2 (A), J22.1 (VBUS), U11.5 (VBUS)
unnamed: J1.2, R2.1
unnamed: C20.1, C22.2, J4.3, R4.1, U10.1 (IP+), U10.2 (IP+), U12.3 (+VO), U13.2 (VO)
unnamed: J7.2, U7.8 (A)
unnamed: J7.3, U7.7 (B)
unnamed: J7.4, U7.6 (Z)
unnamed: J7.5, U7.5 (Y)
unnamed: J16.3 (D+), U6.4 (I/O2)
unnamed: J16.2 (D-), U6.6 (I/O1)
unnamed: J17.2, U1.34 (PA0)
unnamed: J17.3, U1.35 (PA1)
unnamed: J22.3 (D+), U11.4 (I/O2)
unnamed: J22.2 (D-), U11.6 (I/O1)
unnamed: R13.2, R17.1, U4.3 (FB)
unnamed: R14.1, U8.1 (D0)
unnamed: R18.2, U9.7 (A)
unnamed: R19.2, U9.6 (B)
unnamed: R20.2, U9.4 (C)
unnamed: R21.2, U9.2 (D)
unnamed: R25.2, U9.5 (DP)
unnamed: R22.2, U9.1 (E)
unnamed: R23.2, U9.9 (F)
unnamed: R24.2, U9.10 (G)
unnamed: C32.1, U10.6 (FILTER)
unnamed: R15.1, U10.7 (VIOUT)
Vout: C26.1, D10.1 (K), J7.1, R13.1

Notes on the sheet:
tx+
rx-
sw_boot0
Cload = 2*(Cl_crys - Cstray)
uart4_TX uart4_RX
usb_user
tx-
usb_stlink
DC-DC Converter
rx+
